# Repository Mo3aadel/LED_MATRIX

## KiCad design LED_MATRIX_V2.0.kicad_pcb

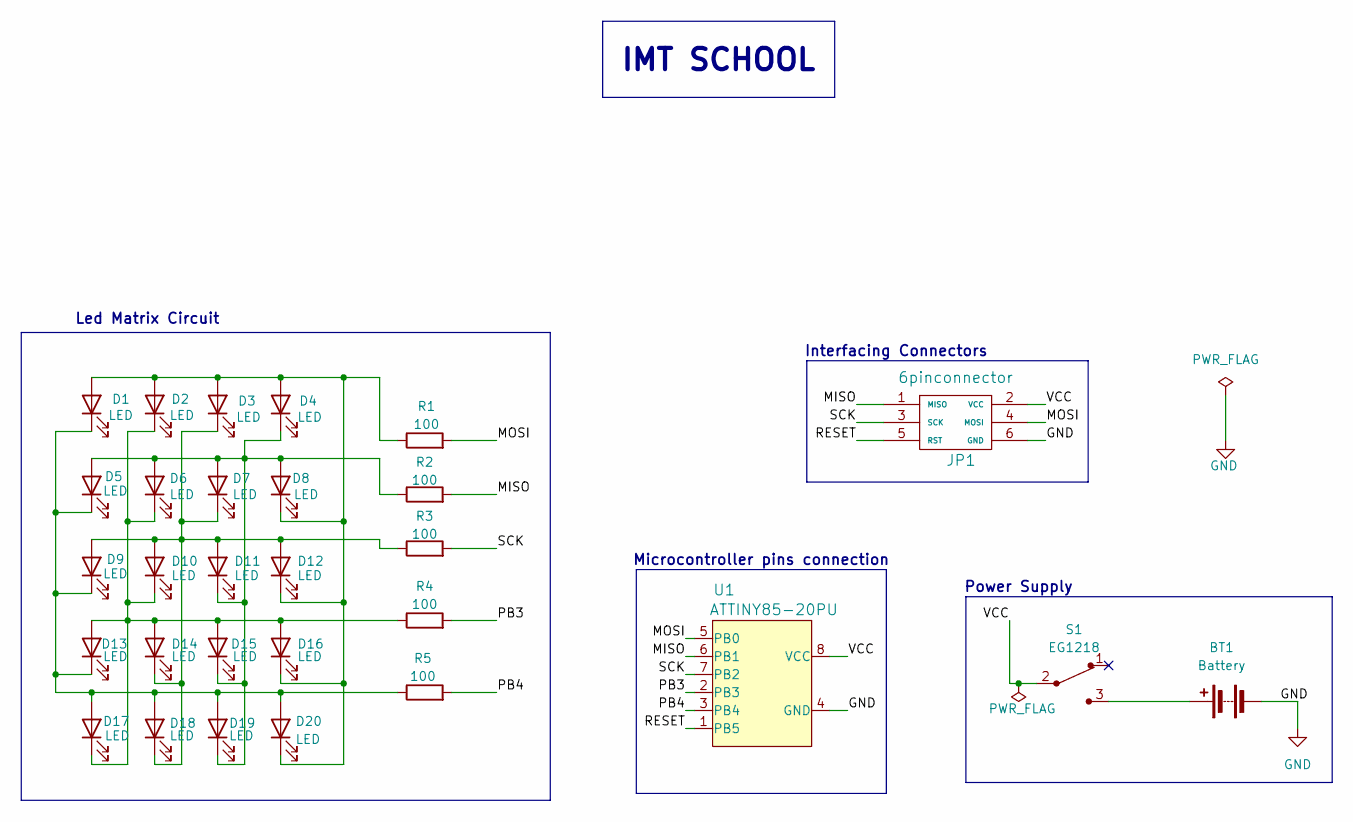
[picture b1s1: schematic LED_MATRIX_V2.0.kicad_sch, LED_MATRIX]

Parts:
BT1: Battery; BatteryHolder_Keystone_1058_1x2032
D1, D2, D3, D4, D5, D6, D7, D8, D9, D10, D11, D12, D13, D14, D15, D16, D17, D18, D19, D20: LED; LED_D3.0mm
JP1: 6pinconnector; PinHeader_1x06_P2.54mm_Vertical
R1, R2, R3, R4, R5: 100; R_Axial_DIN0204_L3.6mm_D1.6mm_P7.62mm_Horizontal
S1: EG1218; Switch_Slide_11.6x4mm_EG1218; MPN EG1218; Digi-Key_PN EG1903-ND
U1: ATTINY85-20PU; DIP-8_W7.62mm; MPN ATTINY85-20PU; Digi-Key_PN ATTINY85-20PU-ND

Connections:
/MISO: JP1.1 (MISO), R2.2, U1.6 (PB1)
/MOSI: JP1.4 (MOSI), R1.2, U1.5 (PB0)
/PB3: R4.2, U1.2 (PB3)
/PB4: R5.2, U1.3 (PB4)
/RESET: JP1.5 (RST), U1.1 (PB5)
/SCK: JP1.3 (SCK), R3.2, U1.7 (PB2)
/VCC: JP1.2 (VCC), S1.2, U1.8 (VCC)
GND: BT1.2 (-), JP1.6 (GND), U1.4 (GND)
unnamed: BT1.1 (+), S1.3
unnamed: D1.2 (A), D2.2 (A), D3.2 (A), D4.2 (A), D8.1 (K), D12.1 (K), D16.1 (K), D20.1 (K), R1.1
unnamed: D1.1 (K), D5.1 (K), D9.1 (K), D13.1 (K), D17.2 (A), D18.2 (A), D19.2 (A), D20.2 (A), R5.1
unnamed: D3.1 (K), D7.1 (K), D9.2 (A), D10.2 (A), D11.2 (A), D12.2 (A), D14.1 (K), D18.1 (K), R3.1
unnamed: D2.1 (K), D6.1 (K), D10.1 (K), D13.2 (A), D14.2 (A), D15.2 (A), D16.2 (A), D17.1 (K), R4.1
unnamed: D4.1 (K), D5.2 (A), D6.2 (A), D7.2 (A), D8.2 (A), D11.1 (K), D15.1 (K), D19.1 (K), R2.1

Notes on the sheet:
IMT SCHOOL
Microcontroller pins connection
Power Supply
Interfacing Connectors
Led Matrix Circuit

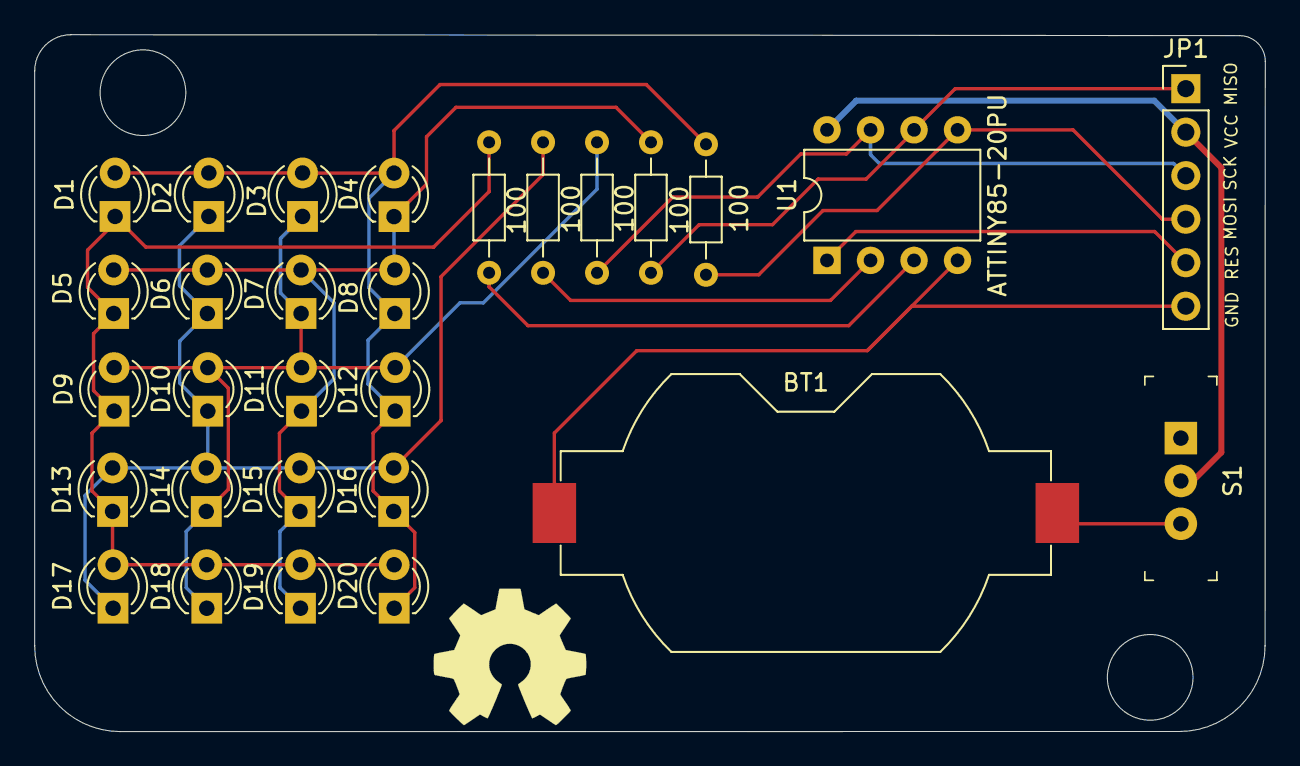
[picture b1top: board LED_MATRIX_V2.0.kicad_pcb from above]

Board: 2 copper layers, 71.8 x 40.7 mm, 29 parts (0 on the bottom side), 14 nets.

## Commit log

2024-12-27 updated the new logo
